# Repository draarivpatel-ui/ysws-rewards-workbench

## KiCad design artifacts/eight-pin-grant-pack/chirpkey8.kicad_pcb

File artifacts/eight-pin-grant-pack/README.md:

# ChirpKey-8: 8-Pin ATtiny412 Acoustic FSK & Capacitive Touch Hardware Token

**ChirpKey-8** is a compact `32 × 24 mm` two-layer custom PCB and `36 × 28 × 7.6 mm` snap-fit pocket enclosure built around the 8-pin **Microchip ATtiny412-SSNR** (`SOIC-8`). It combines a PCB-etched capacitive touch pad (`PA6`), a tactile mode switch (`PA3`), differential push-pull piezo acoustic chirp drive (`PA1` / `PA2`), status LED feedback (`PA7`), and single-wire UPDI programming (`PA0`) on a single 3.3V coin-cell or header-powered board.

- **Live Design Explorer:** [https://aariv.me/chirpkey-8/](https://aariv.me/chirpkey-8/)
- **KiCanvas Verification:** [Open `chirpkey-8` in KiCanvas](https://kicanvas.org/?github=https://github.com/draarivpatel-ui/chirpkey-8)
- **Editable Hardware & CAD Sources:** [`chirpkey8.kicad_pro`](chirpkey8.kicad_pro), [`chirpkey8.kicad_sch`](chirpkey8.kicad_sch), [`chirpkey8.kicad_pcb`](chirpkey8.kicad_pcb), [`cad/chirpkey8_enclosure.step`](cad/chirpkey8_enclosure.step), [`cad/chirpkey8_enclosure.stl`](cad/chirpkey8_enclosure.stl)
- **Firmware & BOM:** [`firmware/chirpkey8.ino`](firmware/chirpkey8.ino), [`bom.csv`](bom.csv), [`bom.json`](bom.json)

---

## Why I Designed ChirpKey-8

Most microcontroller boards lean on high-pin-count USB MCUs even when the task only needs a compact physical trigger and a short, audible/ultrasonic data frame that any laptop or phone microphone can decode without drivers or Bluetooth pairing. By constraining the entire design to the 8-pin **ATtiny412-SSNR** (`SOIC-8`), every single pin has a dedicated hardware role (`VDD`, `GND`, `PA0/UPDI`, `PA1/PIEZO_P`, `PA2/PIEZO_N`, `PA3/MODE_BTN`, `PA6/TOUCH`, and `PA7/LED`), driving the `12 mm` external passive piezo transducer differentially at `6.6 Vpp` from a `3.3 V` rail while keeping the total parts + 3-board OSH Park PCB cost under `$18`.

---

## Project Screenshots & Visual Overview

### 1. Two-Layer Routed PCB (`32 × 24 mm`, `F.Cu` + `B.Cu`)

### 2. KiCad 8 Schematic (`chirpkey8.kicad_sch`)

### 3. Independent KiCanvas Render of Repo Sources

### 4. Interactive Pin Budget & Net Inspector

### 5. Bill of Materials & Budget Breakdown

---

## How to Assemble & Flash

### Step-by-Step Assembly Guide
1. **Inspect bare PCBs:** Check the `32 × 24 mm` 2-layer board (`chirpkey8.kicad_pcb`) for clean `SOIC-8` pads (`U1`) and the exposed copper touch electrode (`TP1`).
2. **Solder SMD passives & MCU (`F.Cu`):** Reflow or hand-solder `U1` (`ATtiny412-SSNR`, aligning Pin 1 dot to the top-left silkscreen marker), decoupling capacitor `C1` (`100 nF 0603`), series resistors `R1` (`330 Ω`), `R2` (`1 MΩ` touch bleed), `R3` (`10 kΩ` pull-up), `R4` (`220 Ω` piezo current limiter), and status LED `D1` (`0603`).
3. **Solder through-hole / tactile parts:** Solder tactile pushbutton `SW1` (`PTS645SM43SMTR92LFS`), external passive piezo transducer `BZ1` (`PKM13EPYH4000-A0`), and the 3-pin 2.54 mm `UPDI + 3V3 + GND` header `J1`.
4. **Mount in 3D-printed enclosure:** Snap the populated `32 × 24 mm` PCB onto the four corner standoffs inside [`cad/chirpkey8_enclosure.stl`](cad/chirpkey8_enclosure.stl) (`36 × 28 × 7.6 mm` shell with UPDI header access window).

### How to Flash Firmware (`firmware/chirpkey8.ino`)
1. Install **megaTinyCore** in Arduino IDE (`https://github.com/SpenceKonde/megaTinyCore`) and select **ATtiny412 / 402** at `20 MHz internal oscillator`.
2. Connect a 3.3V SerialUPDI programmer (`CH340` / `FT232R` + `4.7 kΩ` resistor between `TX` and `RX`) to header `J1` (`Pin 1 = UPDI / PA0`, `Pin 2 = 3V3`, `Pin 3 = GND`).
3. Flash [`firmware/chirpkey8.ino`](firmware/chirpkey8.ino). Pressing `SW1` or touching `TP1` emits an 8-symbol MFSK acoustic chirp frame with CRC-4 checksum across `PA1`/`PA2`.

---

## Bill of Materials (`bom.csv`)

| Ref | Part / Value | Package | Qty | MPN | Supplier | Unit (USD) | Ext (USD) |
|---|---|---|---:|---|---|---:|---:|
| `U1` | ATtiny412-SSNR 8-pin AVR MCU | `SOIC-8` | 1 | `ATTINY412-SSNR` | DigiKey / Microchip | $0.68 | $0.68 |
| `BZ1` | External Passive Piezo Transducer 4 kHz | `12mm THT` | 1 | `PKM13EPYH4000-A0` | DigiKey / Murata | $1.12 | $1.12 |
| `SW1` | Tactile Switch 6x6mm | `SMD 4-Pad` | 1 | `PTS645SM43SMTR92LFS` | DigiKey / C&K | $0.28 | $0.28 |
| `D1` | Green Status LED 0603 | `0603` | 1 | `LTST-C190KGKT` | DigiKey / Lite-On | $0.18 | $0.18 |
| `C1` | 100nF X7R Decoupling Capacitor | `0603` | 1 | `CL10B104KB8NNNC` | DigiKey / Samsung | $0.10 | $0.10 |
| `R1` | 330 Ohm 1% LED Resistor | `0603` | 1 | `RC0603FR-07330RL` | DigiKey / YAGEO | $0.10 | $0.10 |
| `R2` | 1 MOhm 1% Touch Discharge Resistor | `0603` | 1 | `RC0603FR-071ML` | DigiKey / YAGEO | $0.10 | $0.10 |
| `R3` | 10 kOhm 1% Button Pull-Up Resistor | `0603` | 1 | `RC0603FR-0710KL` | DigiKey / YAGEO | $0.10 | $0.10 |
| `R4` | 220 Ohm 1% Piezo Current Limiter | `0603` | 1 | `RC0603FR-07220RL` | DigiKey / YAGEO | $0.10 | $0.10 |
| `J1` | 1x03 2.54mm UPDI + Power Header | `THT 1x03` | 1 | `PREC003SAAN-RC` | DigiKey / Sullins | $0.28 | $0.28 |
| `BT1` | CR2032 Coin Cell Holder | `SMD/THT` | 1 | `BH-800` | DigiKey / MPD | $0.95 | $0.95 |
| `B1` | CR2032 3V Lithium Coin Cell | `20mm` | 1 | `CR2032` | DigiKey / Panasonic | $1.50 | $1.50 |
| `PCB1` | 32x24mm 2-Layer Purple PCB (3-pack) | `32x24mm` | 1 | `OSHPARK-2L-1.19SQIN` | OSH Park | $5.95 | $5.95 |

- **Parts + 3-Board PCB Subtotal:** `$11.44`
- **Estimated Shipping + Tax Allowance:** `$5.96` (`$17.40` estimated grand total)

---

## Known Limitations & Transparency Disclosure

- **Not fabrication-ready.** These KiCad 8 sources, the firmware and every BOM line are design work, not a manufactured, tested board. No PCB has been ordered, assembled, measured or bench-verified, and no acoustic range, battery or touch performance is claimed.
- **AI-Assisted Engineering Disclosure:** This repository was created with AI assistance (`Made with AI` disclosed) and deterministic KiCad 8 / STEP / STL generation tools (`tools/generate.mjs`).
- **Pre-Fabrication Verification Gate:** Before ordering boards, run KiCad 8 native ERC/DRC on `chirpkey8.kicad_pro`, confirm `ATtiny412-SSNR` (`SOIC-8`) and `PKM13EPYH4000-A0` footprints against current datasheets, and test firmware on a current-limited 3.3V bench supply.

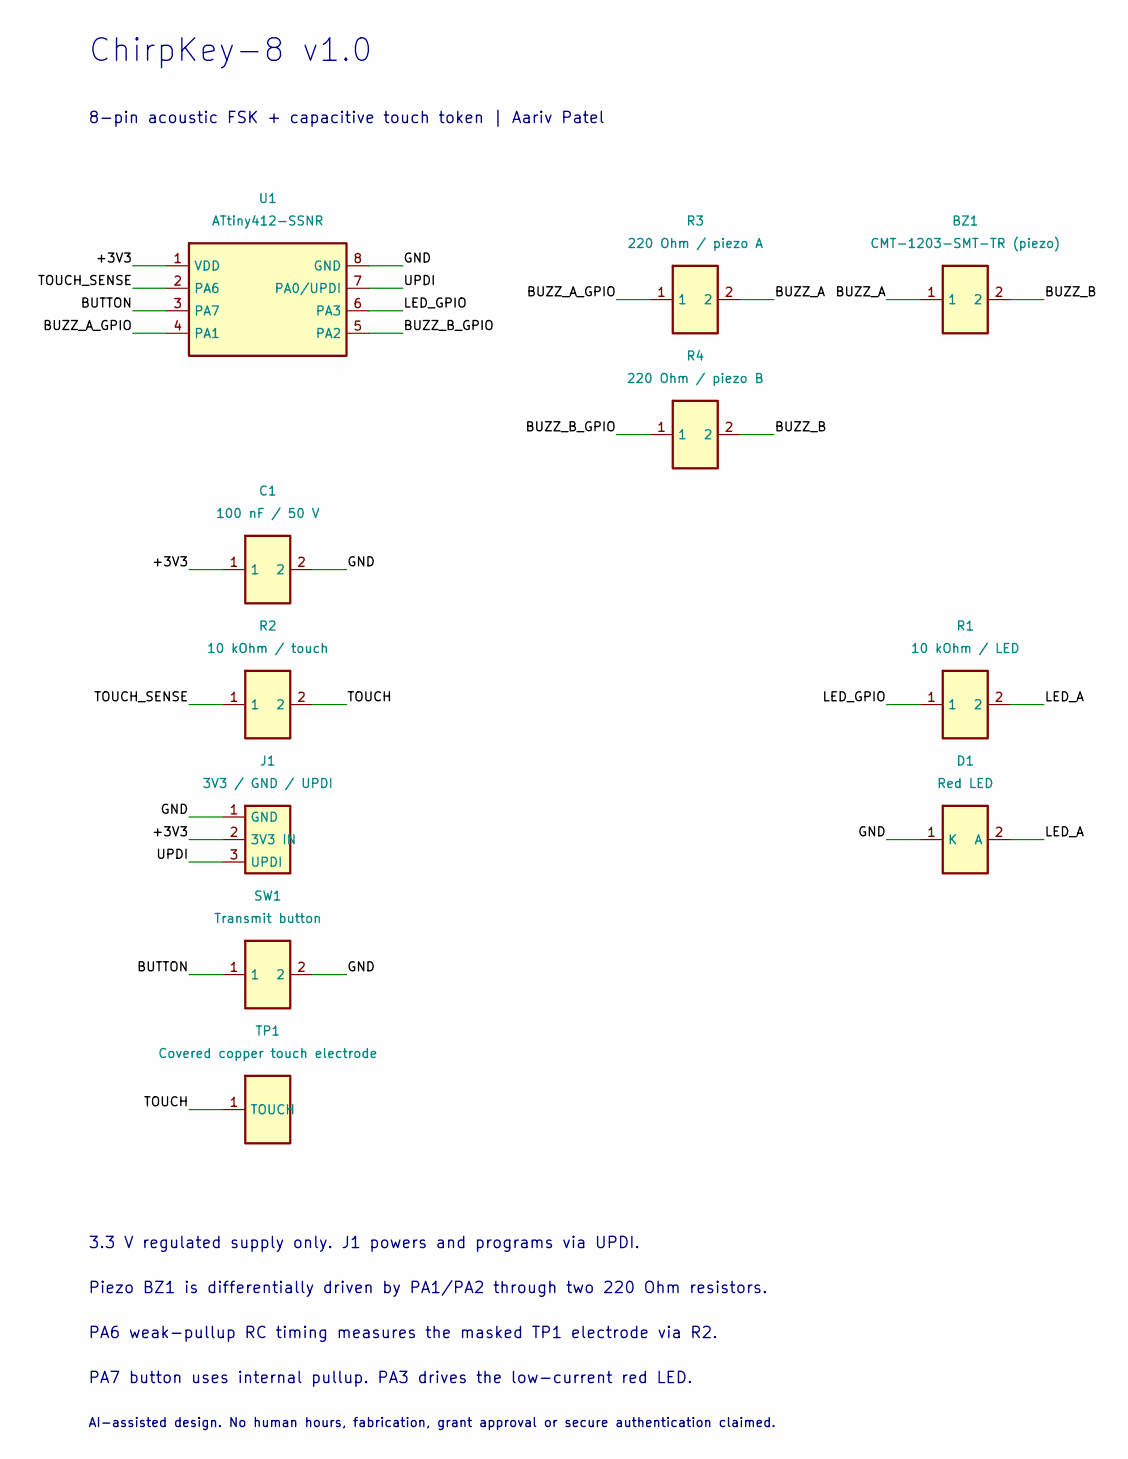
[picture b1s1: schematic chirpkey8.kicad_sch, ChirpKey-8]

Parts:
BZ1: CMT-1203-SMT-TR (piezo); CMT-1203-SMT-TR; Part Number CMT-1203-SMT-TR
C1: 100 nF / 50 V; C_0805; Part Number C0805C104K5RACTU
D1: Red LED; LED_0805; Part Number LTST-C171KRKT
J1: 3V3 / GND / UPDI; PinHeader_1x03_P2.54mm; Part Number M20-9990345
R1: 10 kOhm / LED; R_0805; Part Number RC0805FR-0710KL
R2: 10 kOhm / touch; R_0805; Part Number RC0805FR-0710KL
R3: 220 Ohm / piezo A; R_0805; Part Number RC0805FR-07220RL
R4: 220 Ohm / piezo B; R_0805; Part Number RC0805FR-07220RL
SW1: Transmit button; SW_SPST_B3U-1000P; Part Number B3U-1000P
TP1: Covered copper touch electrode; Touch_D8.4mm; Part Number CHIRPKEY8-PCB-V1.0
U1: ATtiny412-SSNR; SOIC-8_3.9x4.9mm_P1.27mm; Part Number ATtiny412-SSNR

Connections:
+3V3: C1.1, J1.2 (3V3 IN), U1.1 (VDD)
BUTTON: SW1.1, U1.3 (PA7)
BUZZ_A: BZ1.1, R3.2
BUZZ_A_GPIO: R3.1, U1.4 (PA1)
BUZZ_B: BZ1.2, R4.2
BUZZ_B_GPIO: R4.1, U1.5 (PA2)
GND: C1.2, D1.1 (K), J1.1 (GND), SW1.2, U1.8 (GND)
LED_A: D1.2 (A), R1.2
LED_GPIO: R1.1, U1.6 (PA3)
TOUCH: R2.2, TP1.1
TOUCH_SENSE: R2.1, U1.2 (PA6)
UPDI: J1.3 (UPDI), U1.7 (PA0/UPDI)

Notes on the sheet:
ChirpKey-8 v1.0
8-pin acoustic FSK + capacitive touch token | Aariv Patel
3.3 V regulated supply only. J1 powers and programs via UPDI.
Piezo BZ1 is differentially driven by PA1/PA2 through two 220 Ohm resistors.
PA6 weak-pullup RC timing measures the masked TP1 electrode via R2.
PA7 button uses internal pullup. PA3 drives the low-current red LED.
AI-assisted design. No human hours, fabrication, grant approval or secure authentication claimed.

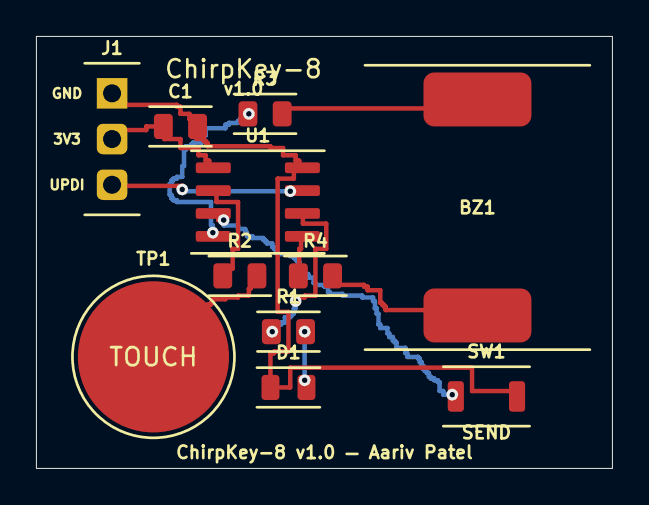
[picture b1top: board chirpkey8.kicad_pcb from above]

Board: 2 copper layers, 32.0 x 24.0 mm, 11 parts (0 on the bottom side), 12 nets.

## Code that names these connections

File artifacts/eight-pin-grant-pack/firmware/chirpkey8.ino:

/* ChirpKey-8 v1.0. Register-level ATtiny412 firmware, AI-assisted.
 * 3.3 V / 10 MHz. Use megaTinyCore, ATtiny412, internal 10 MHz, millis disabled.
 * Burn the 20 MHz oscillator fuse, divide by 2 at runtime, and preserve UPDI.
 * This transmits a public identifier, NOT a password or authentication secret.
 */
#include <avr/io.h>
#include <avr/interrupt.h>
#include <avr/cpufunc.h>
#include <util/delay.h>
#include <stdint.h>

#if !defined(__AVR_ATtiny412__)
#error "Select ATtiny412, not a classic ATtiny85 or another AVR."
#endif
#if F_CPU != 10000000UL
#error "ChirpKey-8 requires F_CPU=10000000UL for safe 3.3 V operation."
#endif

static constexpr uint8_t PIEZO = PIN1_bm | PIN2_bm; // package pins 4 and 5
static constexpr uint8_t LED = PIN3_bm;             // package pin 6
static constexpr uint8_t TOUCH = PIN6_bm;           // package pin 2
static constexpr uint8_t BUTTON = PIN7_bm;          // package pin 3
static constexpr uint16_t SPACE_HZ = 2400;
static constexpr uint16_t MARK_HZ = 3600;
static uint16_t baseline = 0;
static uint8_t sequence = 0, debounce = 0;
static bool armed = true, clockReady = false;

ISR(TCB0_INT_vect) {
  PORTA.OUTTGL = PIEZO; // simultaneous complementary edges, up to 6.6 Vp-p
  TCB0.INTFLAGS = TCB_CAPT_bm;
}

static void silence() {
  TCB0.CTRLA = 0;
  TCB0.INTCTRL = 0;
  TCB0.INTFLAGS = TCB_CAPT_bm;
  PORTA.OUTCLR = PIEZO; // both terminals low, no DC across the piezo
}

static void carrier(uint16_t hz) {
  const uint8_t saved = SREG;
  cli();
  TCB0.CTRLA = 0;
  TCB0.CNT = 0;
  TCB0.CCMP = (uint16_t)((F_CPU + hz) / (2UL * hz) - 1UL);
  TCB0.CTRLB = TCB_CNTMODE_INT_gc;
  TCB0.INTFLAGS = TCB_CAPT_bm;
  PORTA.OUTCLR = PIN2_bm;
  PORTA.OUTSET = PIN1_bm;
  TCB0.INTCTRL = TCB_CAPT_bm;
  TCB0.CTRLA = TCB_CLKSEL_CLKDIV1_gc | TCB_ENABLE_bm;
  SREG = saved;
}

static uint8_t crc8(uint8_t crc, uint8_t data) {
  crc ^= data;
  for (uint8_t bit = 0; bit < 8; bit++)
    crc = (crc & 0x80) ? (uint8_t)((crc << 1) ^ 0x07) : (uint8_t)(crc << 1);
  return crc; // CRC-8/SMBUS, polynomial 0x07, initial 0, no reflection
}

static void sendByte(uint8_t data) {
  // Fixed 16 ms symbols, MSB first. No UART start/stop bits.
  for (uint8_t bit = 0; bit < 8; bit++) {
    carrier((data & 0x80) ? MARK_HZ : SPACE_HZ);
    _delay_ms(16);
    data <<= 1;
  }
}

static void transmit() {
  PORTA.OUTSET = LED;
  for (uint8_t i = 0; i < 4; i++) sendByte(0x55); // acquisition preamble
  sendByte(0xD3);                               // sync, outside CRC
  const uint8_t payload[] = { 0x01, 0x08, 0x41, 0x52, sequence++ };
  uint8_t crc = 0;
  for (uint8_t i = 0; i < sizeof(payload); i++) {
    crc = crc8(crc, payload[i]);
    sendByte(payload[i]);
  }
  sendByte(crc);
  silence();
  PORTA.OUTCLR = LED;
}

static uint16_t touchSample() {
  // Discharge the covered electrode through R2, then release PA6 and time its
  // charge through the internal weak pullup. More capacitance takes longer.
  const uint8_t saved = SREG;
  cli();
  PORTA.PIN6CTRL = 0;
  PORTA.OUTCLR = TOUCH;
  PORTA.DIRSET = TOUCH;
  _delay_us(50);
  PORTA.DIRCLR = TOUCH;
  PORTA.PIN6CTRL = PORT_PULLUPEN_bm; // keep the digital input buffer enabled
  uint16_t count = 0;
  while (!(VPORTA.IN & TOUCH) && count < 512) count++;
  PORTA.PIN6CTRL = 0;
  SREG = saved;
  return count;
}

void setup() {
  cli();
  // At 3.3 V, the MCU's guaranteed speed grade is 10 MHz, not 20 MHz.
  _PROTECTED_WRITE(CLKCTRL.MCLKCTRLA, CLKCTRL_CLKSEL_OSC20M_gc);
  _PROTECTED_WRITE(CLKCTRL.MCLKCTRLB, CLKCTRL_PDIV_2X_gc | CLKCTRL_PEN_bm);
  PORTA.OUTCLR = PIEZO | LED | TOUCH;
  PORTA.DIRSET = PIEZO | LED;
  PORTA.DIRCLR = TOUCH | BUTTON;
  PORTA.PIN7CTRL = PORT_PULLUPEN_bm;
  // PA0's direction/control/fuse is deliberately untouched. UPDI stays usable.
  silence();
  clockReady = (FUSE.OSCCFG & FUSE_FREQSEL_gm) == FUSE_FREQSEL_20MHZ_gc;
  if (clockReady) {
    _delay_ms(100); // keep fingers off TP1 during the calibration window
    uint32_t sum = 0;
    for (uint8_t i = 0; i < 64; i++) { sum += touchSample(); _delay_ms(2); }
    baseline = (uint16_t)(sum / 64);
  }
  sei();
}

void loop() {
  if (!clockReady) { // Wrong oscillator fuse, do not emit incorrect FSK.
    PORTA.OUTTGL = LED;
    _delay_ms(100);
    return;
  }
  const uint16_t sample = touchSample();
  const bool touched = sample < 512 && baseline < 500 && sample > baseline + 4;
  const bool pressed = !(VPORTA.IN & BUTTON);
  if (touched || pressed) {
    if (debounce < 4) debounce++;
    if (debounce == 4 && armed) { armed = false; transmit(); }
  } else {
    if (debounce) debounce--;
    if (!debounce) armed = true;
    // Slow idle-only baseline adaptation. Never adapt while a touch is active.
    if (sample < 512 && armed) baseline = (uint16_t)((31UL * baseline + sample + 16) / 32);
  }
  _delay_ms(5); // ~20 ms debounce; touch sampling is bounded even if shorted
}

#ifdef CHIRPKEY8_STANDALONE
int main() { setup(); for (;;) loop(); }
#endif
